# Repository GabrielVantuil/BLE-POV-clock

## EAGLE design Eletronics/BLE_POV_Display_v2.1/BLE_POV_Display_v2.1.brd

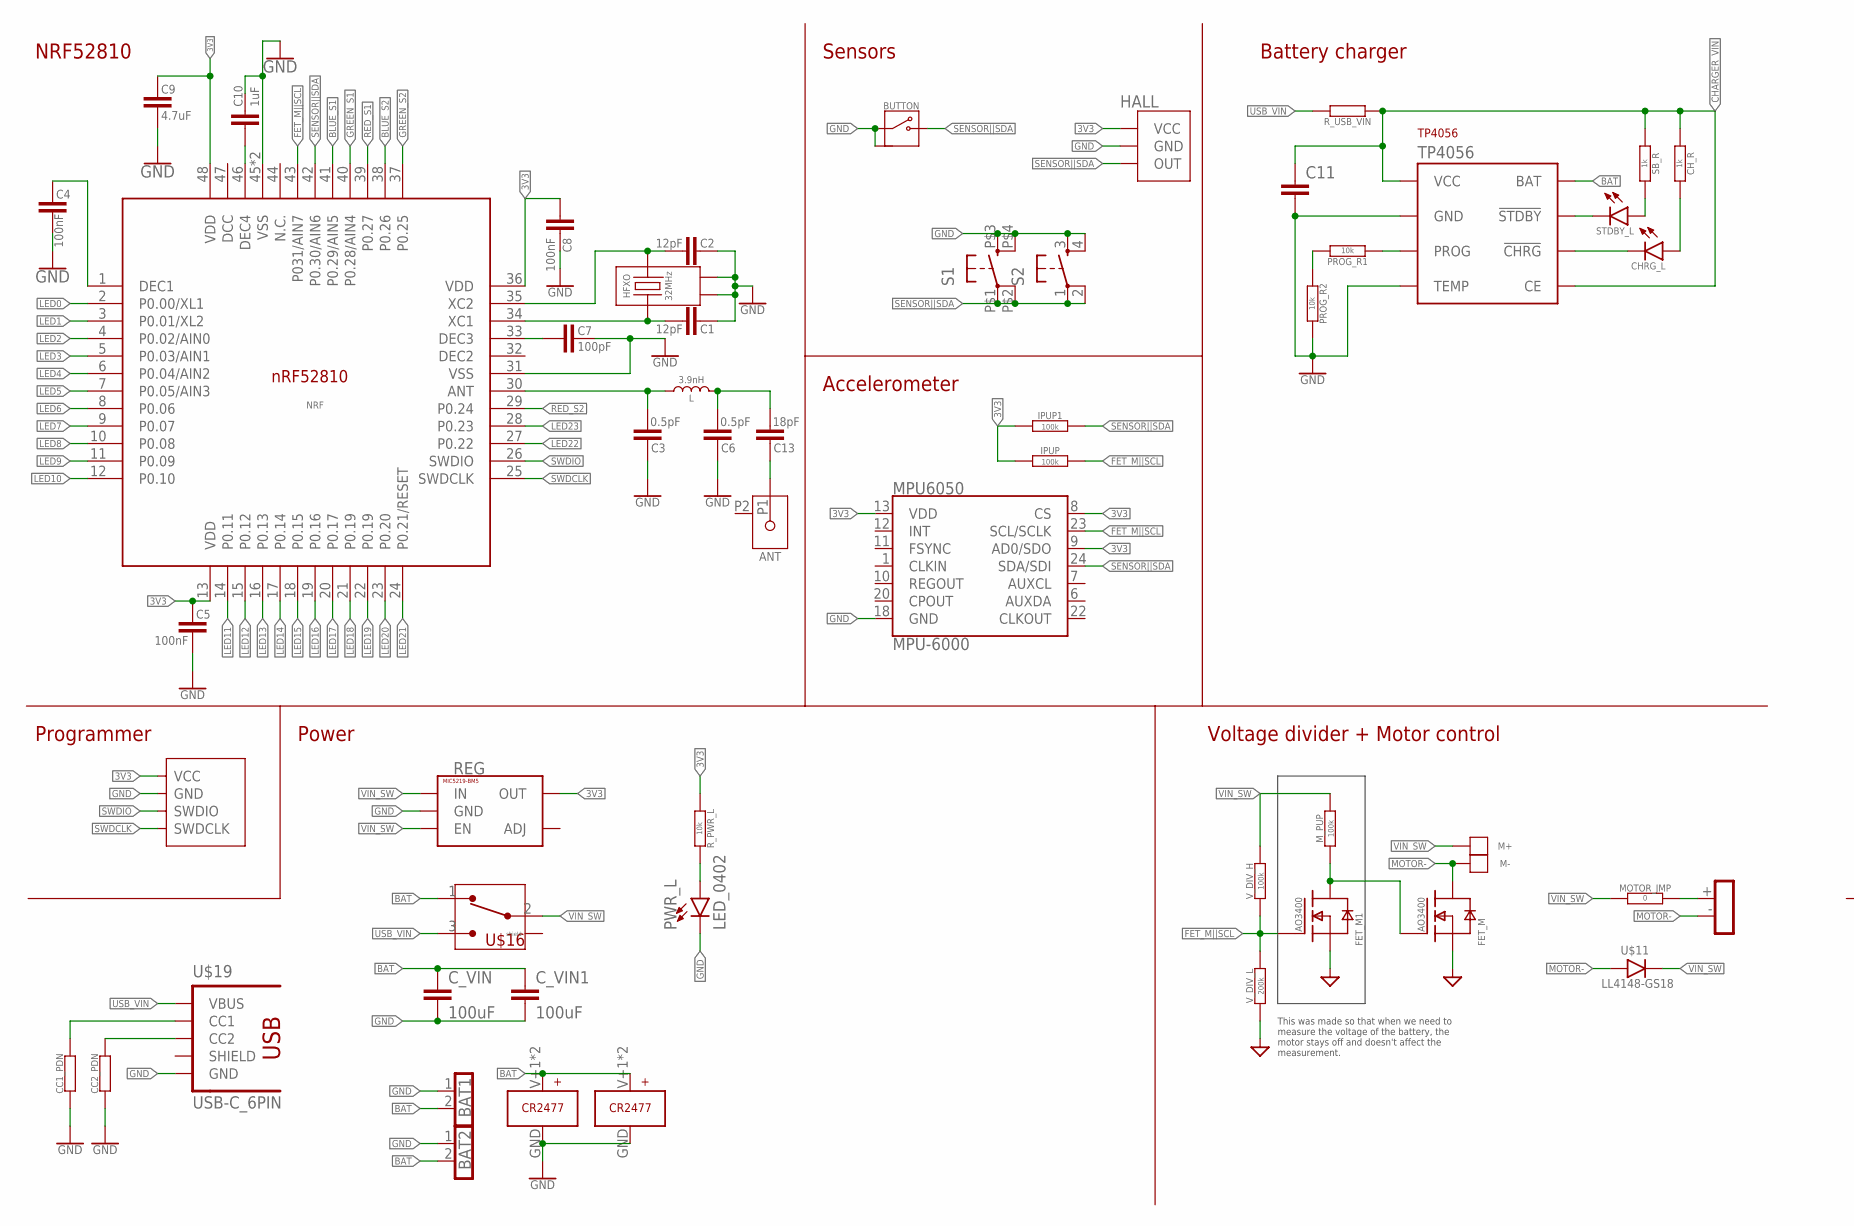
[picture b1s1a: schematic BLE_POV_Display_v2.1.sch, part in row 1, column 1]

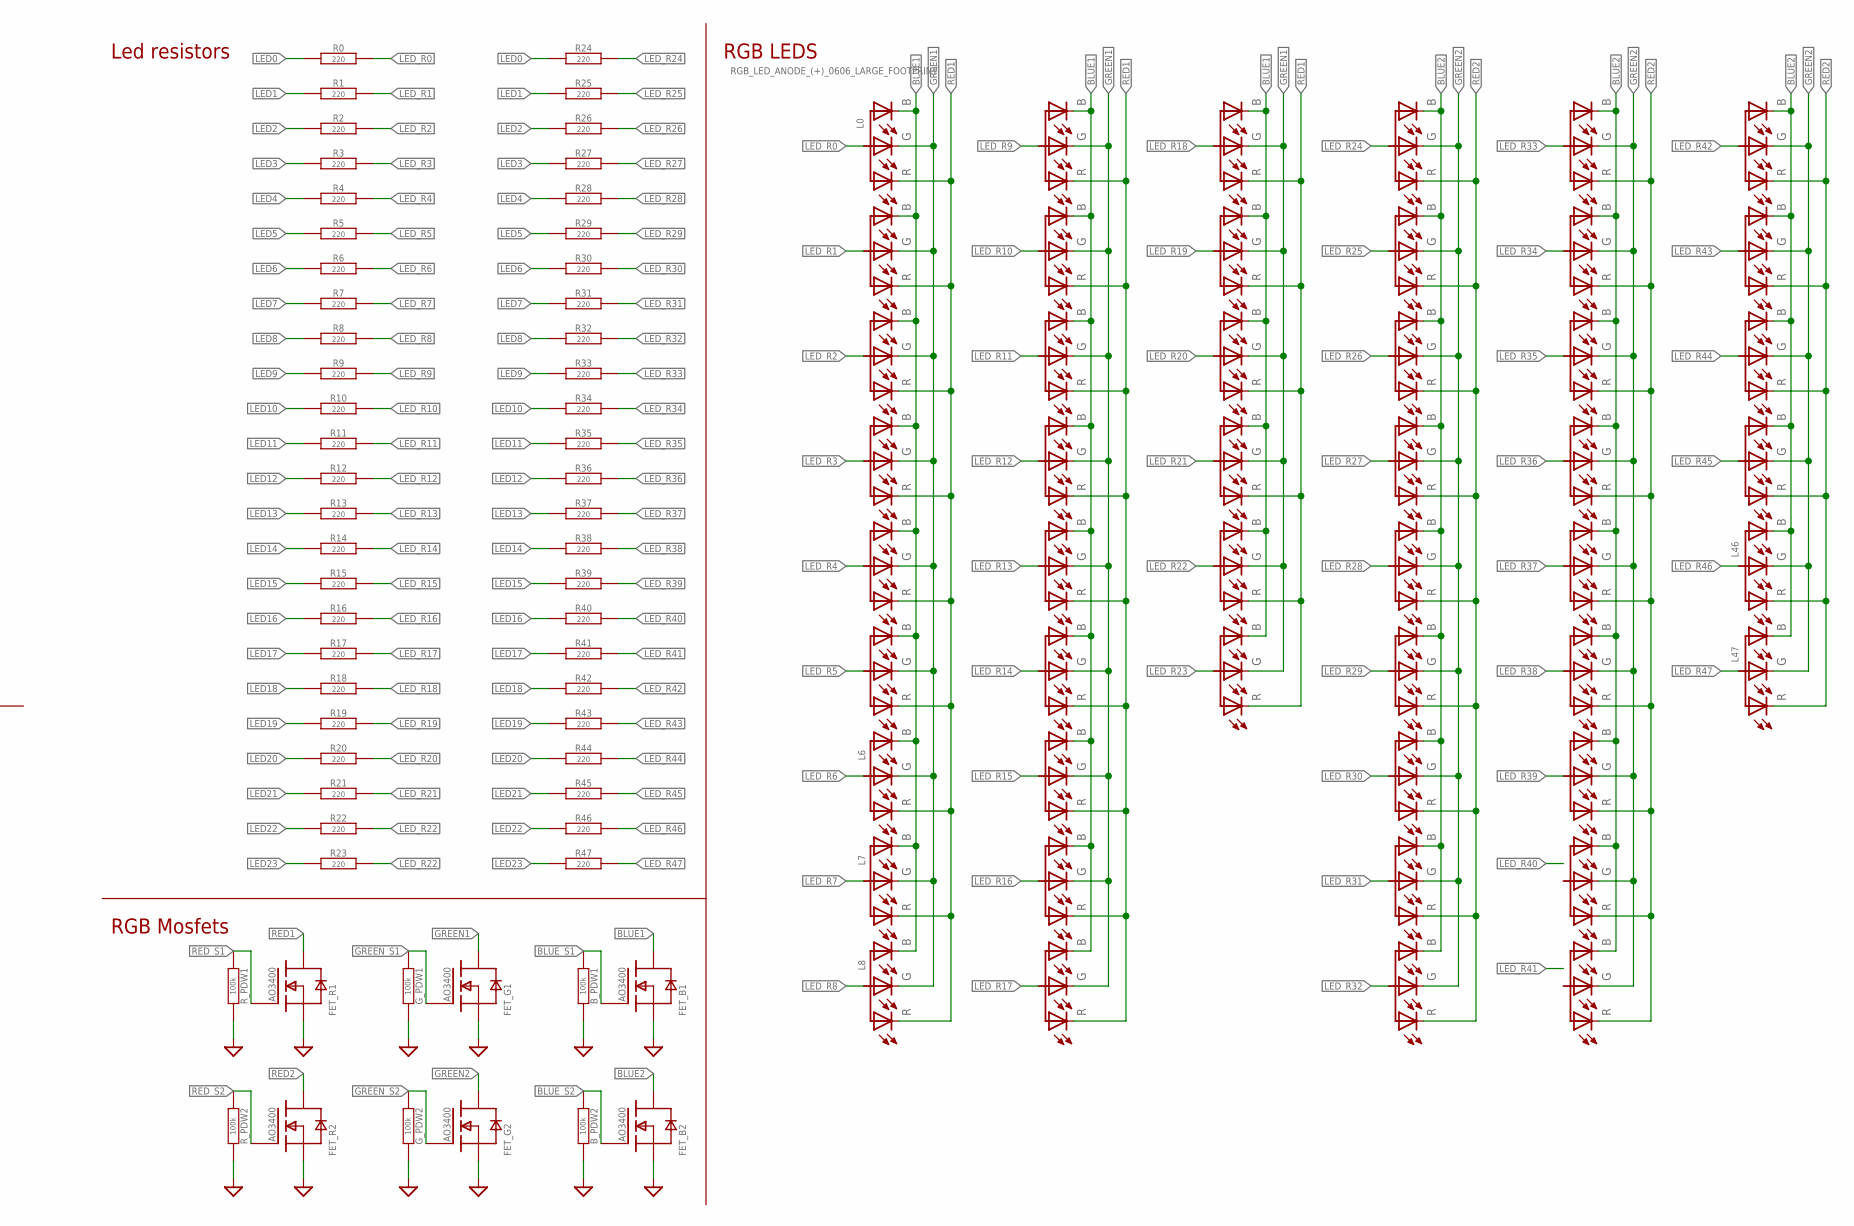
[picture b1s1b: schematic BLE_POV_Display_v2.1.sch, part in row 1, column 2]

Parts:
1: CR2477; CR2477_PTH
ANT: ANT3216LL00R2400A
BAT1, BAT2: PINH1X02; 1X02
BUTTON: PUSHBUTTON_2X4X3.5; 2X4X3.5MM
B_PDW1, B_PDW2: 100k; 0402-RES
C1, C2: 12pF; 0402-CAP
C3, C6: 0.5pF; 0402-CAP
C4, C5, C8: 100nF; 0402-CAP
C7: 100pF; 0402-CAP
C9: 4.7uF; 1206
C10: 1uF; 0402-CAP
C11: CAP0603|1206; 0603|1206
C13: 18pF; 0402-CAP
CC1_PDN, CC2_PDN: RESISTOR0603-RES; 0603-RES
CHRG_L: LED_0402; 0402
CH_R: 1k; 0402-RES
C_VIN, C_VIN1: 100uF; 1206
FET_B1, FET_B2: AO3400; SOT23-3
FET_G1, FET_G2: AO3400; SOT23-3
FET_M, FET_M1: AO3400; SOT23-3
FET_R1, FET_R2: AO3400; SOT23-3
G_PDW1, G_PDW2: 100k; 0402-RES
HALL: 49E; TO92_HALLSENSOR
HFXO: 32MHz; XTAL_CX2016DB16000D0WZRC1
IPUP, IPUP1: 100k; 0402-RES
L: 3.9nH; 0402
L0, L1, L2, L3, L4, L5, L6, L7, L8, L9, L10, L11, L12, L13, L14, L15, L16, L17, L18, L19, L20, L21, L22, L23, L24, L25, L26, L27, L28, L29, L30, L31, L32, L33, L34, L35, L36, L37, L38, L39, L40, L41, L42, L43, L44, L45, L46, L47: RGB_LED_ANODE_(+)_0606_LARGE_FOOTPRINT; 0606
LIR2450: CR2477; CR2477_PTH
M+: PAD_50X100MIL
M-: PAD_50X100MIL
MOTOR_JMP: 0; 0402-RES
MPU6050: MPU-6000; QFN-24-EP
M_PUP: 100k; 0402-RES
NRF: NORDIC_NRF_NRF52810_QF; NRF52810_QFN40P600X600X90-48_N_3MMTHERMAL
PROG_R1, PROG_R2: 10k; 0603-RES
PWR_L: LED_0402; 0402
R0, R1, R2, R3, R4, R5, R6, R7, R8, R9, R10, R11, R12, R13, R14, R15, R16, R17, R18, R19, R20, R21, R22, R23, R24, R25, R26, R27, R28, R29, R30, R31, R32, R33, R34, R35, R36, R37, R38, R39, R40, R41, R42, R43, R44, R45, R46, R47: 220; 0402-RES
REG: MIC5219-BM5; SOT23-5
R_PDW1, R_PDW2: 100k; 0402-RES
R_PWR_L: 10k; 0402-RES
R_USB_VIN: RESISTOR1206; 1206
S1: BT_4_PIN_12X12MM_SMD; 12X12MM_SMD_BT
S2: BT_4_PINSMD; DTS-6_SMD
SB_R: 1k; 0402-RES
STDBY_L: LED_0402; 0402
TP4056: TP4056_SOP8; SOP8
U$2: GV_SWD_4P; GV_SWD_1.27MM_4P_SEMI_SMD
U$11: LL4148-GS18; SOD-80
U$16: SMD_SWITCH
U$19: USB-C_6PIN; USCX-06FX-XXMX-01
U$22: MOTOR-24.5X12.3
V_DIV_H: 100k; 0402-RES
V_DIV_L: 200k; 0402-RES

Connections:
3V3: C5.1, C8.2, C9.1, HALL.VCC, IPUP.1, IPUP1.1, MPU6050.8 (CS), MPU6050.9 (AD0/SDO), MPU6050.13 (VDD), NRF.13 (VDD), NRF.36 (VDD), NRF.48 (VDD), REG.5 (OUT), R_PWR_L.1, U$2.VCC
BAT: 1.V+1 (V+), 1.V+2 (V+), BAT1.2, BAT2.2, C_VIN.1, C_VIN1.1, LIR2450.V+1 (V+), LIR2450.V+2 (V+), TP4056.P$5 (BAT), U$16.1
BLUE1: FET_B1.3 (D), L0.1 (LED_BLUE), L1.1 (LED_BLUE), L2.1 (LED_BLUE), L3.1 (LED_BLUE), L4.1 (LED_BLUE), L5.1 (LED_BLUE), L6.1 (LED_BLUE), L7.1 (LED_BLUE), L8.1 (LED_BLUE), L9.1 (LED_BLUE), L10.1 (LED_BLUE), L11.1 (LED_BLUE), L12.1 (LED_BLUE), L13.1 (LED_BLUE), L14.1 (LED_BLUE), L15.1 (LED_BLUE), L16.1 (LED_BLUE), L17.1 (LED_BLUE), L18.1 (LED_BLUE), L19.1 (LED_BLUE), L20.1 (LED_BLUE), L21.1 (LED_BLUE), L22.1 (LED_BLUE), L23.1 (LED_BLUE)
BLUE2: FET_B2.3 (D), L24.1 (LED_BLUE), L25.1 (LED_BLUE), L26.1 (LED_BLUE), L27.1 (LED_BLUE), L28.1 (LED_BLUE), L29.1 (LED_BLUE), L30.1 (LED_BLUE), L31.1 (LED_BLUE), L32.1 (LED_BLUE), L33.1 (LED_BLUE), L34.1 (LED_BLUE), L35.1 (LED_BLUE), L36.1 (LED_BLUE), L37.1 (LED_BLUE), L38.1 (LED_BLUE), L39.1 (LED_BLUE), L40.1 (LED_BLUE), L41.1 (LED_BLUE), L42.1 (LED_BLUE), L43.1 (LED_BLUE), L44.1 (LED_BLUE), L45.1 (LED_BLUE), L46.1 (LED_BLUE), L47.1 (LED_BLUE)
BLUE_S1: B_PDW1.1, FET_B1.1 (G), NRF.41 (P0.29/AIN5)
BLUE_S2: B_PDW2.1, FET_B2.1 (G), NRF.38 (P0.26)
CHARGER_VIN: C11.1, C11.P$1 (1), CH_R.1, R_USB_VIN.1, SB_R.1, TP4056.P$4 (VCC), TP4056.P$8 (CE)
FET_M||SCL: FET_M1.1 (G), IPUP.2, MPU6050.23 (SCL/SCLK), NRF.43 (P031/AIN7), V_DIV_H.2, V_DIV_L.2
GND: 1.GND, BAT1.1, BAT2.1, BUTTON.2, BUTTON.GND, BUTTON.GND2 (GND), B_PDW1.2, B_PDW2.2, C1.1, C2.1, C3.2, C4.2, C5.2, C6.2, C7.1, C8.1, C9.2, C10.1, C11.2, C11.P$2 (2), CC1_PDN.1, CC2_PDN.1, C_VIN.2, C_VIN1.2, FET_B1.2 (S), FET_B2.2 (S), FET_G1.2 (S), FET_G2.2 (S), FET_M.2 (S), FET_M1.2 (S), FET_R1.2 (S), FET_R2.2 (S), G_PDW1.2, G_PDW2.2, HALL.GND, HFXO.2, HFXO.4, LIR2450.GND, MPU6050.18 (GND), NRF.31 (VSS), NRF.45 (VSS), NRF.PAD (VSS), PROG_R2.2, PWR_L.C, REG.2 (GND), R_PDW1.2, R_PDW2.2, S1.P$3 (3), S1.P$4 (4), S2.3, S2.4, TP4056.P$1 (TEMP), TP4056.P$3 (GND), U$2.GND, U$19.GND1 (GND), U$19.GND2 (GND), V_DIV_L.1
GREEN1: FET_G1.3 (D), L0.4 (LED_GREEN), L1.4 (LED_GREEN), L2.4 (LED_GREEN), L3.4 (LED_GREEN), L4.4 (LED_GREEN), L5.4 (LED_GREEN), L6.4 (LED_GREEN), L7.4 (LED_GREEN), L8.4 (LED_GREEN), L9.4 (LED_GREEN), L10.4 (LED_GREEN), L11.4 (LED_GREEN), L12.4 (LED_GREEN), L13.4 (LED_GREEN), L14.4 (LED_GREEN), L15.4 (LED_GREEN), L16.4 (LED_GREEN), L17.4 (LED_GREEN), L18.4 (LED_GREEN), L19.4 (LED_GREEN), L20.4 (LED_GREEN), L21.4 (LED_GREEN), L22.4 (LED_GREEN), L23.4 (LED_GREEN)
GREEN2: FET_G2.3 (D), L24.4 (LED_GREEN), L25.4 (LED_GREEN), L26.4 (LED_GREEN), L27.4 (LED_GREEN), L28.4 (LED_GREEN), L29.4 (LED_GREEN), L30.4 (LED_GREEN), L31.4 (LED_GREEN), L32.4 (LED_GREEN), L33.4 (LED_GREEN), L34.4 (LED_GREEN), L35.4 (LED_GREEN), L36.4 (LED_GREEN), L37.4 (LED_GREEN), L38.4 (LED_GREEN), L39.4 (LED_GREEN), L40.4 (LED_GREEN), L41.4 (LED_GREEN), L42.4 (LED_GREEN), L43.4 (LED_GREEN), L44.4 (LED_GREEN), L45.4 (LED_GREEN), L46.4 (LED_GREEN), L47.4 (LED_GREEN)
GREEN_S1: FET_G1.1 (G), G_PDW1.1, NRF.40 (P0.28/AIN4)
GREEN_S2: FET_G2.1 (G), G_PDW2.1, NRF.37 (P0.25)
LED0: NRF.2 (P0.00/XL1), R0.1, R24.1
LED1: NRF.3 (P0.01/XL2), R1.1, R25.1
LED2: NRF.4 (P0.02/AIN0), R2.1, R26.1
LED3: NRF.5 (P0.03/AIN1), R3.1, R27.1
LED4: NRF.6 (P0.04/AIN2), R4.1, R28.1
LED5: NRF.7 (P0.05/AIN3), R5.1, R29.1
LED6: NRF.8 (P0.06), R6.1, R30.1
LED7: NRF.9 (P0.07), R7.1, R31.1
LED8: NRF.10 (P0.08), R8.1, R32.1
LED9: NRF.11 (P0.09), R9.1, R33.1
LED10: NRF.12 (P0.10), R10.1, R34.1
LED11: NRF.14 (P0.11), R11.1, R35.1
LED12: NRF.15 (P0.12), R12.1, R36.1
LED13: NRF.16 (P0.13), R13.1, R37.1
LED14: NRF.17 (P0.14), R14.1, R38.1
LED15: NRF.18 (P0.15), R15.1, R39.1
LED16: NRF.19 (P0.16), R16.1, R40.1
LED17: NRF.20 (P0.17), R17.1, R41.1
LED18: NRF.21 (P0.19), R18.1, R42.1
LED19: NRF.22 (P0.19), R19.1, R43.1
LED20: NRF.23 (P0.20), R20.1, R44.1
LED21: NRF.24 (P0.21/RESET), R21.1, R45.1
LED22: NRF.27 (P0.22), R22.1, R46.1
LED23: NRF.28 (P0.23), R23.1, R47.1
LED_R0: L0.2 (COMMON_ANODE), R0.2
LED_R1: L1.2 (COMMON_ANODE), R1.2
LED_R2: L2.2 (COMMON_ANODE), R2.2
LED_R3: L3.2 (COMMON_ANODE), R3.2
LED_R4: L4.2 (COMMON_ANODE), R4.2
LED_R5: L5.2 (COMMON_ANODE), R5.2
LED_R6: L6.2 (COMMON_ANODE), R6.2
LED_R7: L7.2 (COMMON_ANODE), R7.2
LED_R8: L8.2 (COMMON_ANODE), R8.2
LED_R9: L9.2 (COMMON_ANODE), R9.2
LED_R10: L10.2 (COMMON_ANODE), R10.2
LED_R11: L11.2 (COMMON_ANODE), R11.2
LED_R12: L12.2 (COMMON_ANODE), R12.2
LED_R13: L13.2 (COMMON_ANODE), R13.2
LED_R14: L14.2 (COMMON_ANODE), R14.2
LED_R15: L15.2 (COMMON_ANODE), R15.2
LED_R16: L16.2 (COMMON_ANODE), R16.2
LED_R17: L17.2 (COMMON_ANODE), R17.2
LED_R18: L18.2 (COMMON_ANODE), R18.2
LED_R19: L19.2 (COMMON_ANODE), R19.2
LED_R20: L20.2 (COMMON_ANODE), R20.2
LED_R21: L21.2 (COMMON_ANODE), R21.2
LED_R22: L22.2 (COMMON_ANODE), R22.2, R23.2
LED_R23: L23.2 (COMMON_ANODE)
LED_R24: L24.2 (COMMON_ANODE), R24.2
LED_R25: L25.2 (COMMON_ANODE), R25.2
LED_R26: L26.2 (COMMON_ANODE), R26.2
LED_R27: L27.2 (COMMON_ANODE), R27.2
LED_R28: L28.2 (COMMON_ANODE), R28.2
LED_R29: L29.2 (COMMON_ANODE), R29.2
LED_R30: L30.2 (COMMON_ANODE), R30.2
LED_R31: L31.2 (COMMON_ANODE), R31.2
LED_R32: L32.2 (COMMON_ANODE), R32.2
LED_R33: L33.2 (COMMON_ANODE), R33.2
LED_R34: L34.2 (COMMON_ANODE), R34.2
LED_R35: L35.2 (COMMON_ANODE), R35.2
LED_R36: L36.2 (COMMON_ANODE), R36.2
LED_R37: L37.2 (COMMON_ANODE), R37.2
LED_R38: L38.2 (COMMON_ANODE), R38.2
LED_R39: L39.2 (COMMON_ANODE), R39.2
LED_R40: R40.2
LED_R41: R41.2
LED_R42: L42.2 (COMMON_ANODE), R42.2
LED_R43: L43.2 (COMMON_ANODE), R43.2
LED_R44: L44.2 (COMMON_ANODE), R44.2
LED_R45: L45.2 (COMMON_ANODE), R45.2
LED_R46: L46.2 (COMMON_ANODE), R46.2
LED_R47: L47.2 (COMMON_ANODE), R47.2
MOTOR-: FET_M.3 (D), M-.P$1, U$11.+, U$22.- (CW-)
unnamed: C1.2, HFXO.3, NRF.34 (XC1)
unnamed: C2.2, HFXO.1, NRF.35 (XC2)
unnamed: C7.2, NRF.33 (DEC3)
unnamed: CC2_PDN.2, U$19.CC2
unnamed: PROG_R1.2, PROG_R2.1
unnamed: CHRG_L.C, TP4056.P$7 (!CHRG)
unnamed: STDBY_L.C, TP4056.P$6 (!STDBY)
unnamed: C10.2, NRF.46 (DEC4)
unnamed: CC1_PDN.2, U$19.CC1
unnamed: C3.1, L.1, NRF.30 (ANT)
unnamed: C4.1, NRF.1 (DEC1)
unnamed: FET_M.1 (G), FET_M1.3 (D), M_PUP.1
unnamed: MOTOR_JMP.1, U$22.+ (CW+)
unnamed: PROG_R1.1, TP4056.P$2 (PROG)
unnamed: SB_R.2, STDBY_L.A
unnamed: CHRG_L.A, CH_R.2
unnamed: C6.1, C13.1, L.2
unnamed: ANT.P1, C13.2
unnamed: PWR_L.A, R_PWR_L.2
RED1: FET_R1.3 (D), L0.3 (LED_RED), L1.3 (LED_RED), L2.3 (LED_RED), L3.3 (LED_RED), L4.3 (LED_RED), L5.3 (LED_RED), L6.3 (LED_RED), L7.3 (LED_RED), L8.3 (LED_RED), L9.3 (LED_RED), L10.3 (LED_RED), L11.3 (LED_RED), L12.3 (LED_RED), L13.3 (LED_RED), L14.3 (LED_RED), L15.3 (LED_RED), L16.3 (LED_RED), L17.3 (LED_RED), L18.3 (LED_RED), L19.3 (LED_RED), L20.3 (LED_RED), L21.3 (LED_RED), L22.3 (LED_RED), L23.3 (LED_RED)
RED2: FET_R2.3 (D), L24.3 (LED_RED), L25.3 (LED_RED), L26.3 (LED_RED), L27.3 (LED_RED), L28.3 (LED_RED), L29.3 (LED_RED), L30.3 (LED_RED), L31.3 (LED_RED), L32.3 (LED_RED), L33.3 (LED_RED), L34.3 (LED_RED), L35.3 (LED_RED), L36.3 (LED_RED), L37.3 (LED_RED), L38.3 (LED_RED), L39.3 (LED_RED), L40.3 (LED_RED), L41.3 (LED_RED), L42.3 (LED_RED), L43.3 (LED_RED), L44.3 (LED_RED), L45.3 (LED_RED), L46.3 (LED_RED), L47.3 (LED_RED)
RED_S1: FET_R1.1 (G), NRF.39 (P0.27), R_PDW1.1
RED_S2: FET_R2.1 (G), NRF.29 (P0.24), R_PDW2.1
SENSOR||SDA: BUTTON.1, HALL.OUT, IPUP1.2, MPU6050.24 (SDA/SDI), NRF.42 (P0.30/AIN6), S1.P$1 (1), S1.P$2 (2), S2.1, S2.2
SHIELD: U$19.SHIELD1 (SHIELD), U$19.SHIELD2 (SHIELD), U$19.SHIELD3 (SHIELD), U$19.SHIELD4 (SHIELD)
SWDCLK: NRF.25 (SWDCLK), U$2.SWDCLK
SWDIO: NRF.26 (SWDIO), U$2.SWDIO
USB_VIN: R_USB_VIN.2, U$16.3, U$19.VBUS1 (VBUS), U$19.VBUS2 (VBUS)
VIN_SW: M+.P$1, MOTOR_JMP.2, M_PUP.2, REG.1 (IN), REG.3 (EN), U$11.-, U$16.2, V_DIV_H.1

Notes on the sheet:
NRF52810
Voltage divider + Motor control
Programmer
Power
Accelerometer
Sensors
RGB Mosfets
Led resistors
RGB LEDS
Battery charger
This was made so that when we need to measure the voltage of the battery, the motor stays off and doesn't affect the measurement.

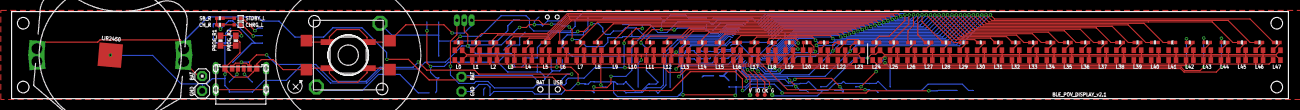
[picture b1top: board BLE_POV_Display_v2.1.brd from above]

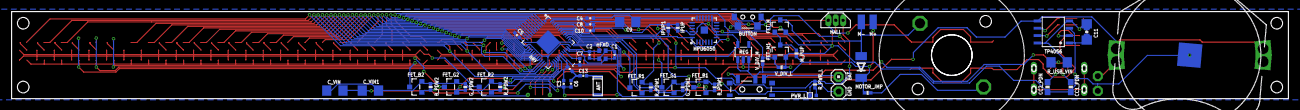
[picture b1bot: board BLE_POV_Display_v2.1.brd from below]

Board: 2 copper layers, 220.0 x 15.0 mm, 165 parts (54 on the bottom side), 112 nets.

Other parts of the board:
U$7: GV_5MM_METAL
U$20: MOTOR-24.5_HOLES

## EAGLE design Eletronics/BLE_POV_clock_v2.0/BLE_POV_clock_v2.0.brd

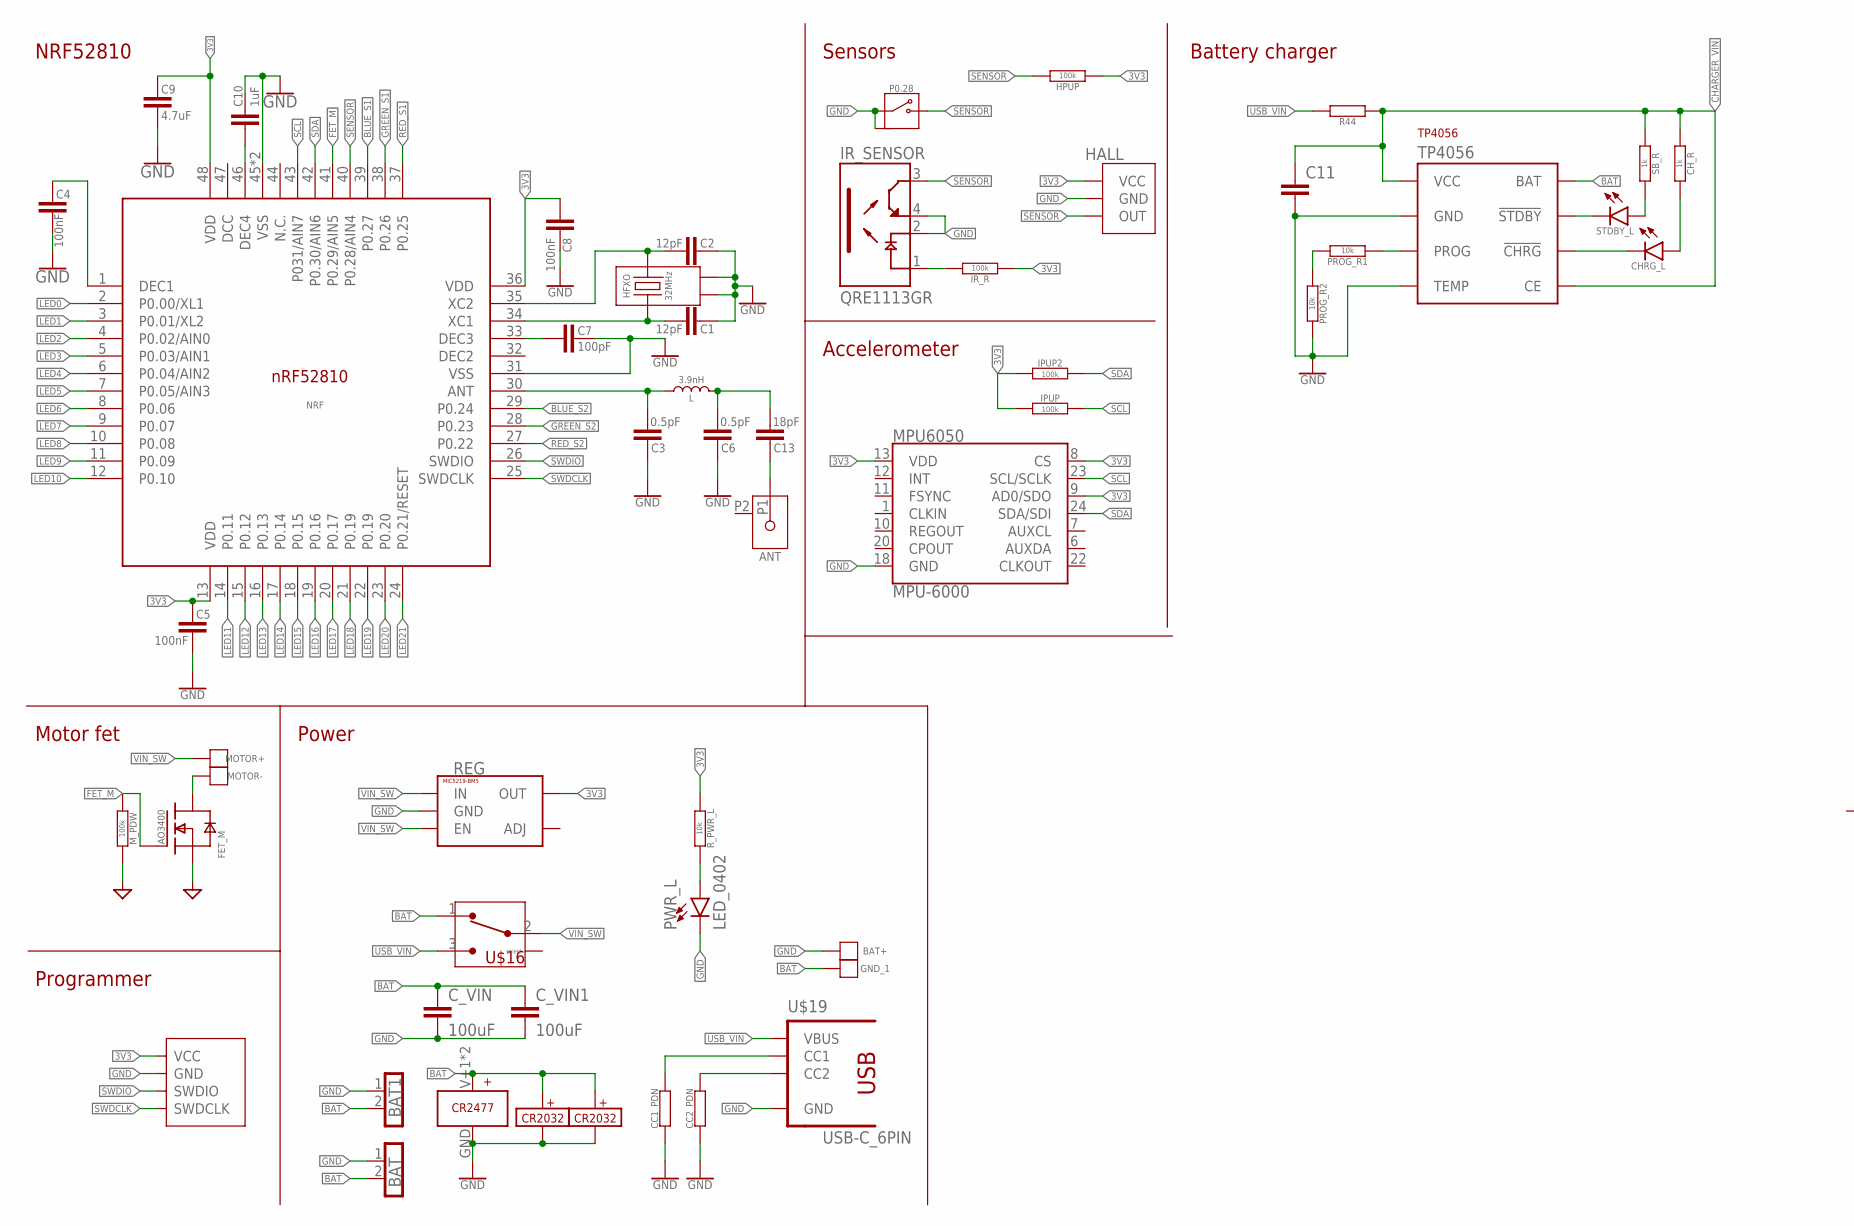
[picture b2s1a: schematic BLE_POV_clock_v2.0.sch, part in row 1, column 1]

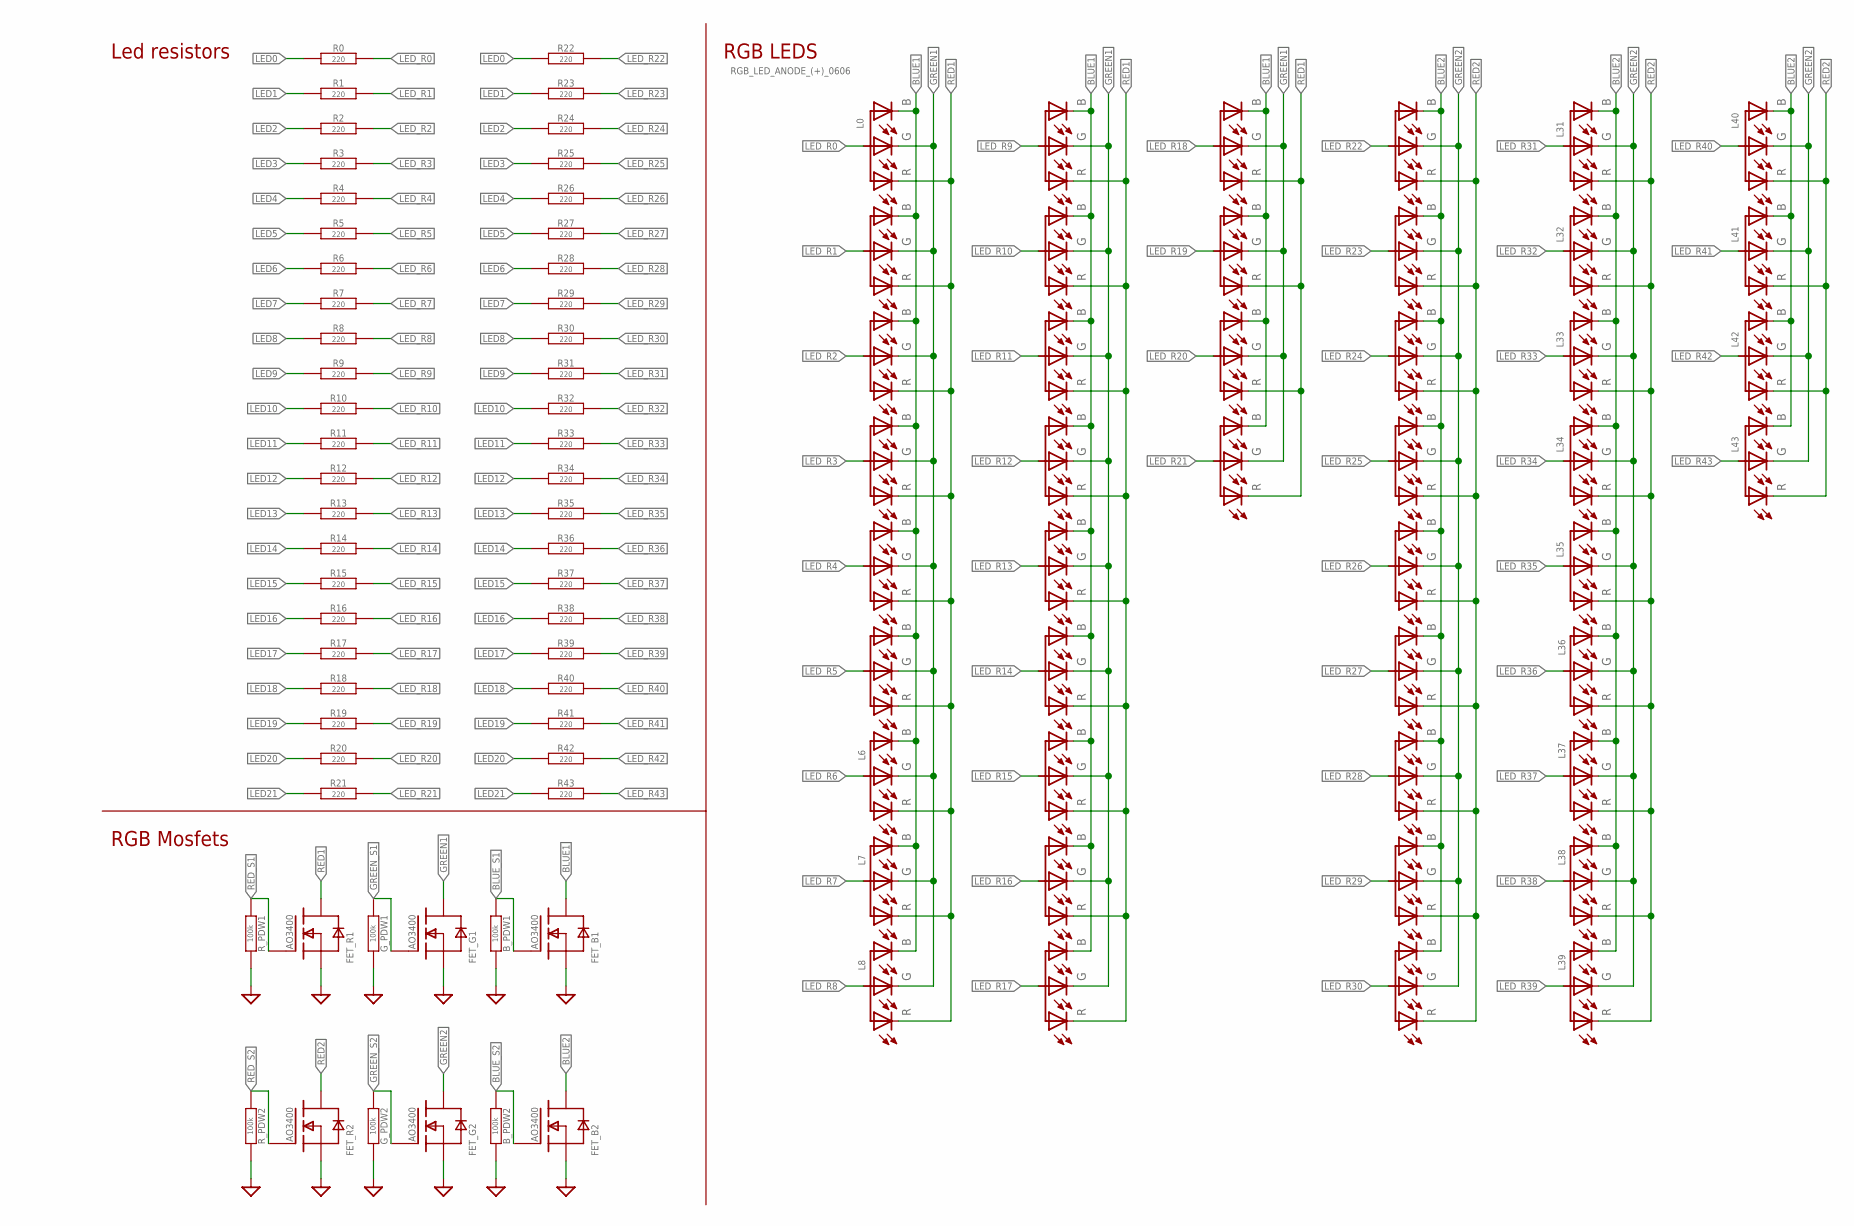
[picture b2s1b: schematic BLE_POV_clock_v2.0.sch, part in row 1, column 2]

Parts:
2477: CR2477; CR2477_PTH
ANT: ANT3216LL00R2400A
BAT, BAT1: PINH1X02; 1X02
BAT+: PAD_50X100MIL
B_PDW1, B_PDW2: 100k; 0402-RES
C1, C2: 12pF; 0402-CAP
C3, C6: 0.5pF; 0402-CAP
C4, C5, C8: 100nF; 0402-CAP
C7: 100pF; 0402-CAP
C9: 4.7uF; 1206
C10: 1uF; 0402-CAP
C11: CAP0603|1206; 0603|1206
C13: 18pF; 0402-CAP
CC1_PDN, CC2_PDN: RESISTOR0603-RES; 0603-RES
CHRG_L: LED_0402; 0402
CH_R: 1k; 0402-RES
C_VIN, C_VIN1: 100uF; 1206
FET_B1, FET_B2: AO3400; SOT23-3
FET_G1, FET_G2: AO3400; SOT23-3
FET_M: AO3400; SOT23-3
FET_R1, FET_R2: AO3400; SOT23-3
GND_1: PAD_50X100MIL
G_PDW1, G_PDW2: 100k; 0402-RES
HALL: 49E; TO92_HALLSENSOR
HFXO: 32MHz; XTAL_CX2016DB16000D0WZRC1
HPUP: 100k; 0402-RES
IPUP, IPUP2: 100k; 0402-RES
IR_R: 100k; 0402-RES
IR_SENSOR: QRE1113GR; SOIC180P460X187-4N
L: 3.9nH; 0402
L0, L1, L2, L3, L4, L5, L6, L7, L8, L9, L10, L11, L12, L13, L14, L15, L16, L17, L18, L19, L20, L21, L22, L23, L24, L25, L26, L27, L28, L29, L30, L31, L32, L33, L34, L35, L36, L37, L38, L39, L40, L41, L42, L43: RGB_LED_ANODE_(+)_0606; LED_RGB_0606
MOTOR+: PAD_50X100MIL
MOTOR-: PAD_50X100MIL
MPU6050: MPU-6000; QFN-24-EP
M_PDW: 100k; 0402-RES
NRF: NORDIC_NRF_NRF52810_QF; NRF52810_QFN40P600X600X90-48_N_3MMTHERMAL
P0.28: PUSHBUTTON_2X4X3.5; 2X4X3.5MM
PROG_R1, PROG_R2: 10k; 0402-RES
PWR_L: LED_0402; 0402
R0, R1, R2, R3, R4, R5, R6, R7, R8, R9, R10, R11, R12, R13, R14, R15, R16, R17, R18, R19, R20, R21, R22, R23, R24, R25, R26, R27, R28, R29, R30, R31, R32, R33, R34, R35, R36, R37, R38, R39, R40, R41, R42, R43: 220; 0402-RES
R44: RESISTOR0603-RES; 0603-RES
REG: MIC5219-BM5; SOT23-5
R_PDW1, R_PDW2: 100k; 0402-RES
R_PWR_L: 10k; 0402-RES
SB_R: 1k; 0402-RES
STDBY_L: LED_0402; 0402
TP4056: TP4056_SOP8; SOP8
U$2: GV_SWD_4P; GV_SWD_1.27MM_4P_SEMI_SMD
U$11: CR2032CHINA; CR2032_CHINA_HOLDER
U$16: SMD_SWITCH
U$19: USB-C_6PIN; USCX-06FX-XXMX-01
U$20: CR2032-SMD; CR2032

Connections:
3V3: C5.1, C8.2, C9.1, HALL.VCC, HPUP.1, IPUP.1, IPUP2.1, IR_R.1, MPU6050.8 (CS), MPU6050.9 (AD0/SDO), MPU6050.13 (VDD), NRF.13 (VDD), NRF.36 (VDD), NRF.48 (VDD), REG.5 (OUT), R_PWR_L.1, U$2.VCC
BAT: 2477.V+1 (V+), 2477.V+2 (V+), BAT.2, BAT1.2, C_VIN.1, C_VIN1.1, GND_1.P$1, TP4056.P$5 (BAT), U$11.+1 (+), U$11.+2 (+), U$16.1, U$20.V+5 (+), U$20.V+6 (+)
BLUE1: FET_B1.3 (D), L0.B (LED_BLUE), L1.B (LED_BLUE), L2.B (LED_BLUE), L3.B (LED_BLUE), L4.B (LED_BLUE), L5.B (LED_BLUE), L6.B (LED_BLUE), L7.B (LED_BLUE), L8.B (LED_BLUE), L9.B (LED_BLUE), L10.B (LED_BLUE), L11.B (LED_BLUE), L12.B (LED_BLUE), L13.B (LED_BLUE), L14.B (LED_BLUE), L15.B (LED_BLUE), L16.B (LED_BLUE), L17.B (LED_BLUE), L18.B (LED_BLUE), L19.B (LED_BLUE), L20.B (LED_BLUE), L21.B (LED_BLUE)
BLUE2: FET_B2.3 (D), L22.B (LED_BLUE), L23.B (LED_BLUE), L24.B (LED_BLUE), L25.B (LED_BLUE), L26.B (LED_BLUE), L27.B (LED_BLUE), L28.B (LED_BLUE), L29.B (LED_BLUE), L30.B (LED_BLUE), L31.B (LED_BLUE), L32.B (LED_BLUE), L33.B (LED_BLUE), L34.B (LED_BLUE), L35.B (LED_BLUE), L36.B (LED_BLUE), L37.B (LED_BLUE), L38.B (LED_BLUE), L39.B (LED_BLUE), L40.B (LED_BLUE), L41.B (LED_BLUE), L42.B (LED_BLUE), L43.B (LED_BLUE)
BLUE_S1: B_PDW1.1, FET_B1.1 (G), NRF.39 (P0.27)
BLUE_S2: B_PDW2.1, FET_B2.1 (G), NRF.29 (P0.24)
CHARGER_VIN: C11.1, C11.P$1 (1), CH_R.1, R44.1, SB_R.1, TP4056.P$4 (VCC), TP4056.P$8 (CE)
FET_M: FET_M.1 (G), M_PDW.1, NRF.41 (P0.29/AIN5)
GND: 2477.GND, BAT.1, BAT1.1, BAT+.P$1, B_PDW1.2, B_PDW2.2, C1.1, C2.1, C3.2, C4.2, C5.2, C6.2, C7.1, C8.1, C9.2, C10.1, C11.2, C11.P$2 (2), CC1_PDN.1, CC2_PDN.1, C_VIN.2, C_VIN1.2, FET_B1.2 (S), FET_B2.2 (S), FET_G1.2 (S), FET_G2.2 (S), FET_M.2 (S), FET_R1.2 (S), FET_R2.2 (S), G_PDW1.2, G_PDW2.2, HALL.GND, HFXO.2, HFXO.4, IR_SENSOR.2 (C), IR_SENSOR.4 (ET), MPU6050.18 (GND), M_PDW.2, NRF.31 (VSS), NRF.45 (VSS), NRF.PAD (VSS), P0.28.2, P0.28.GND, P0.28.GND2 (GND), PROG_R2.2, PWR_L.C, REG.2 (GND), R_PDW1.2, R_PDW2.2, TP4056.P$1 (TEMP), TP4056.P$3 (GND), U$2.GND, U$11.-, U$19.GND1 (GND), U$19.GND2 (GND), U$19.SHIELD1 (GND), U$19.SHIELD2 (GND), U$19.SHIELD3 (GND), U$19.SHIELD4 (GND), U$20.GND (-)
GREEN1: FET_G1.3 (D), L0.G (LED_GREEN), L1.G (LED_GREEN), L2.G (LED_GREEN), L3.G (LED_GREEN), L4.G (LED_GREEN), L5.G (LED_GREEN), L6.G (LED_GREEN), L7.G (LED_GREEN), L8.G (LED_GREEN), L9.G (LED_GREEN), L10.G (LED_GREEN), L11.G (LED_GREEN), L12.G (LED_GREEN), L13.G (LED_GREEN), L14.G (LED_GREEN), L15.G (LED_GREEN), L16.G (LED_GREEN), L17.G (LED_GREEN), L18.G (LED_GREEN), L19.G (LED_GREEN), L20.G (LED_GREEN), L21.G (LED_GREEN)
GREEN2: FET_G2.3 (D), L22.G (LED_GREEN), L23.G (LED_GREEN), L24.G (LED_GREEN), L25.G (LED_GREEN), L26.G (LED_GREEN), L27.G (LED_GREEN), L28.G (LED_GREEN), L29.G (LED_GREEN), L30.G (LED_GREEN), L31.G (LED_GREEN), L32.G (LED_GREEN), L33.G (LED_GREEN), L34.G (LED_GREEN), L35.G (LED_GREEN), L36.G (LED_GREEN), L37.G (LED_GREEN), L38.G (LED_GREEN), L39.G (LED_GREEN), L40.G (LED_GREEN), L41.G (LED_GREEN), L42.G (LED_GREEN), L43.G (LED_GREEN)
GREEN_S1: FET_G1.1 (G), G_PDW1.1, NRF.38 (P0.26)
GREEN_S2: FET_G2.1 (G), G_PDW2.1, NRF.28 (P0.23)
LED0: NRF.2 (P0.00/XL1), R0.1, R22.1
LED1: NRF.3 (P0.01/XL2), R1.1, R23.1
LED2: NRF.4 (P0.02/AIN0), R2.1, R24.1
LED3: NRF.5 (P0.03/AIN1), R3.1, R25.1
LED4: NRF.6 (P0.04/AIN2), R4.1, R26.1
LED5: NRF.7 (P0.05/AIN3), R5.1, R27.1
LED6: NRF.8 (P0.06), R6.1, R28.1
LED7: NRF.9 (P0.07), R7.1, R29.1
LED8: NRF.10 (P0.08), R8.1, R30.1
LED9: NRF.11 (P0.09), R9.1, R31.1
LED10: NRF.12 (P0.10), R10.1, R32.1
LED11: NRF.14 (P0.11), R11.1, R33.1
LED12: NRF.15 (P0.12), R12.1, R34.1
LED13: NRF.16 (P0.13), R13.1, R35.1
LED14: NRF.17 (P0.14), R14.1, R36.1
LED15: NRF.18 (P0.15), R15.1, R37.1
LED16: NRF.19 (P0.16), R16.1, R38.1
LED17: NRF.20 (P0.17), R17.1, R39.1
LED18: NRF.21 (P0.19), R18.1, R40.1
LED19: NRF.22 (P0.19), R19.1, R41.1
LED20: NRF.23 (P0.20), R20.1, R42.1
LED21: NRF.24 (P0.21/RESET), R21.1, R43.1
LED_R0: L0.COM (COMMON_ANODE), R0.2
LED_R1: L1.COM (COMMON_ANODE), R1.2
LED_R2: L2.COM (COMMON_ANODE), R2.2
LED_R3: L3.COM (COMMON_ANODE), R3.2
LED_R4: L4.COM (COMMON_ANODE), R4.2
LED_R5: L5.COM (COMMON_ANODE), R5.2
LED_R6: L6.COM (COMMON_ANODE), R6.2
LED_R7: L7.COM (COMMON_ANODE), R7.2
LED_R8: L8.COM (COMMON_ANODE), R8.2
LED_R9: L9.COM (COMMON_ANODE), R9.2
LED_R10: L10.COM (COMMON_ANODE), R10.2
LED_R11: L11.COM (COMMON_ANODE), R11.2
LED_R12: L12.COM (COMMON_ANODE), R12.2
LED_R13: L13.COM (COMMON_ANODE), R13.2
LED_R14: L14.COM (COMMON_ANODE), R14.2
LED_R15: L15.COM (COMMON_ANODE), R15.2
LED_R16: L16.COM (COMMON_ANODE), R16.2
LED_R17: L17.COM (COMMON_ANODE), R17.2
LED_R18: L18.COM (COMMON_ANODE), R18.2
LED_R19: L19.COM (COMMON_ANODE), R19.2
LED_R20: L20.COM (COMMON_ANODE), R20.2
LED_R21: L21.COM (COMMON_ANODE), R21.2
LED_R22: L22.COM (COMMON_ANODE), R22.2
LED_R23: L23.COM (COMMON_ANODE), R23.2
LED_R24: L24.COM (COMMON_ANODE), R24.2
LED_R25: L25.COM (COMMON_ANODE), R25.2
LED_R26: L26.COM (COMMON_ANODE), R26.2
LED_R27: L27.COM (COMMON_ANODE), R27.2
LED_R28: L28.COM (COMMON_ANODE), R28.2
LED_R29: L29.COM (COMMON_ANODE), R29.2
LED_R30: L30.COM (COMMON_ANODE), R30.2
LED_R31: L31.COM (COMMON_ANODE), R31.2
LED_R32: L32.COM (COMMON_ANODE), R32.2
LED_R33: L33.COM (COMMON_ANODE), R33.2
LED_R34: L34.COM (COMMON_ANODE), R34.2
LED_R35: L35.COM (COMMON_ANODE), R35.2
LED_R36: L36.COM (COMMON_ANODE), R36.2
LED_R37: L37.COM (COMMON_ANODE), R37.2
LED_R38: L38.COM (COMMON_ANODE), R38.2
LED_R39: L39.COM (COMMON_ANODE), R39.2
LED_R40: L40.COM (COMMON_ANODE), R40.2
LED_R41: L41.COM (COMMON_ANODE), R41.2
LED_R42: L42.COM (COMMON_ANODE), R42.2
LED_R43: L43.COM (COMMON_ANODE), R43.2
MOTOR: FET_M.3 (D), MOTOR-.P$1
unnamed: C1.2, HFXO.3, NRF.34 (XC1)
unnamed: C2.2, HFXO.1, NRF.35 (XC2)
unnamed: C7.2, NRF.33 (DEC3)
unnamed: CC2_PDN.2, U$19.CC2
unnamed: PROG_R1.2, PROG_R2.1
unnamed: CHRG_L.C, TP4056.P$7 (!CHRG)
unnamed: STDBY_L.C, TP4056.P$6 (!STDBY)
unnamed: C10.2, NRF.46 (DEC4)
unnamed: CC1_PDN.2, U$19.CC1
unnamed: C3.1, L.1, NRF.30 (ANT)
unnamed: C4.1, NRF.1 (DEC1)
unnamed: IR_R.2, IR_SENSOR.1 (A)
unnamed: PROG_R1.1, TP4056.P$2 (PROG)
unnamed: SB_R.2, STDBY_L.A
unnamed: CHRG_L.A, CH_R.2
unnamed: C6.1, C13.1, L.2
unnamed: ANT.P1, C13.2
unnamed: PWR_L.A, R_PWR_L.2
RED1: FET_R1.3 (D), L0.R (LED_RED), L1.R (LED_RED), L2.R (LED_RED), L3.R (LED_RED), L4.R (LED_RED), L5.R (LED_RED), L6.R (LED_RED), L7.R (LED_RED), L8.R (LED_RED), L9.R (LED_RED), L10.R (LED_RED), L11.R (LED_RED), L12.R (LED_RED), L13.R (LED_RED), L14.R (LED_RED), L15.R (LED_RED), L16.R (LED_RED), L17.R (LED_RED), L18.R (LED_RED), L19.R (LED_RED), L20.R (LED_RED), L21.R (LED_RED)
RED2: FET_R2.3 (D), L22.R (LED_RED), L23.R (LED_RED), L24.R (LED_RED), L25.R (LED_RED), L26.R (LED_RED), L27.R (LED_RED), L28.R (LED_RED), L29.R (LED_RED), L30.R (LED_RED), L31.R (LED_RED), L32.R (LED_RED), L33.R (LED_RED), L34.R (LED_RED), L35.R (LED_RED), L36.R (LED_RED), L37.R (LED_RED), L38.R (LED_RED), L39.R (LED_RED), L40.R (LED_RED), L41.R (LED_RED), L42.R (LED_RED), L43.R (LED_RED)
RED_S1: FET_R1.1 (G), NRF.37 (P0.25), R_PDW1.1
RED_S2: FET_R2.1 (G), NRF.27 (P0.22), R_PDW2.1
SCL: IPUP.2, MPU6050.23 (SCL/SCLK), NRF.43 (P031/AIN7)
SDA: IPUP2.2, MPU6050.24 (SDA/SDI), NRF.42 (P0.30/AIN6)
SENSOR: HALL.OUT, HPUP.2, IR_SENSOR.3 (CT), NRF.40 (P0.28/AIN4), P0.28.1
SWDCLK: NRF.25 (SWDCLK), U$2.SWDCLK
SWDIO: NRF.26 (SWDIO), U$2.SWDIO
USB_VIN: R44.2, U$16.3, U$19.VBUS1 (VBUS), U$19.VBUS2 (VBUS)
VIN_SW: MOTOR+.P$1, REG.1 (IN), REG.3 (EN), U$16.2

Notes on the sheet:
NRF52810
Motor fet
Programmer
Power
Accelerometer
Sensors
RGB Mosfets
Led resistors
RGB LEDS
Battery charger

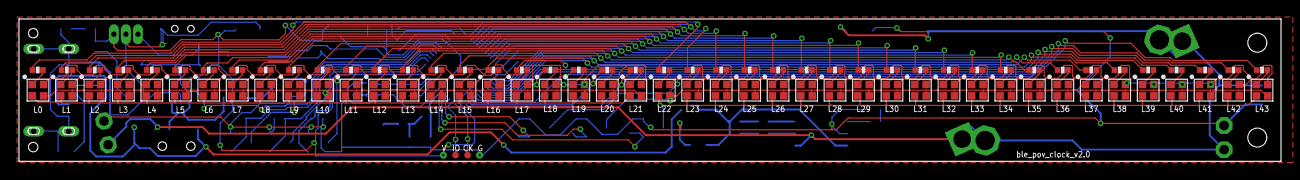
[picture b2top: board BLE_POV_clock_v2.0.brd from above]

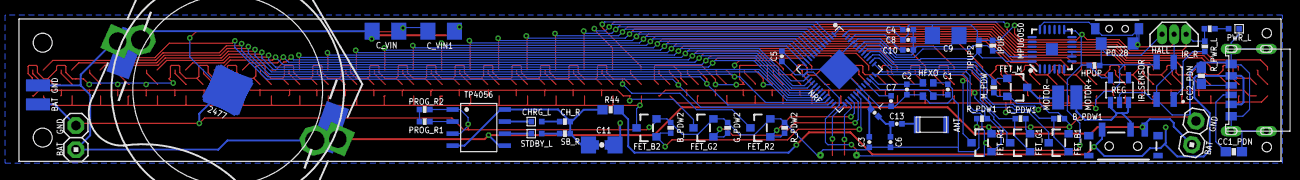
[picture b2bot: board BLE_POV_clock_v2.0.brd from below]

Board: 2 copper layers, 133.0 x 15.0 mm, 154 parts (64 on the bottom side), 109 nets.

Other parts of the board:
U$7: GV_5MM_METAL
